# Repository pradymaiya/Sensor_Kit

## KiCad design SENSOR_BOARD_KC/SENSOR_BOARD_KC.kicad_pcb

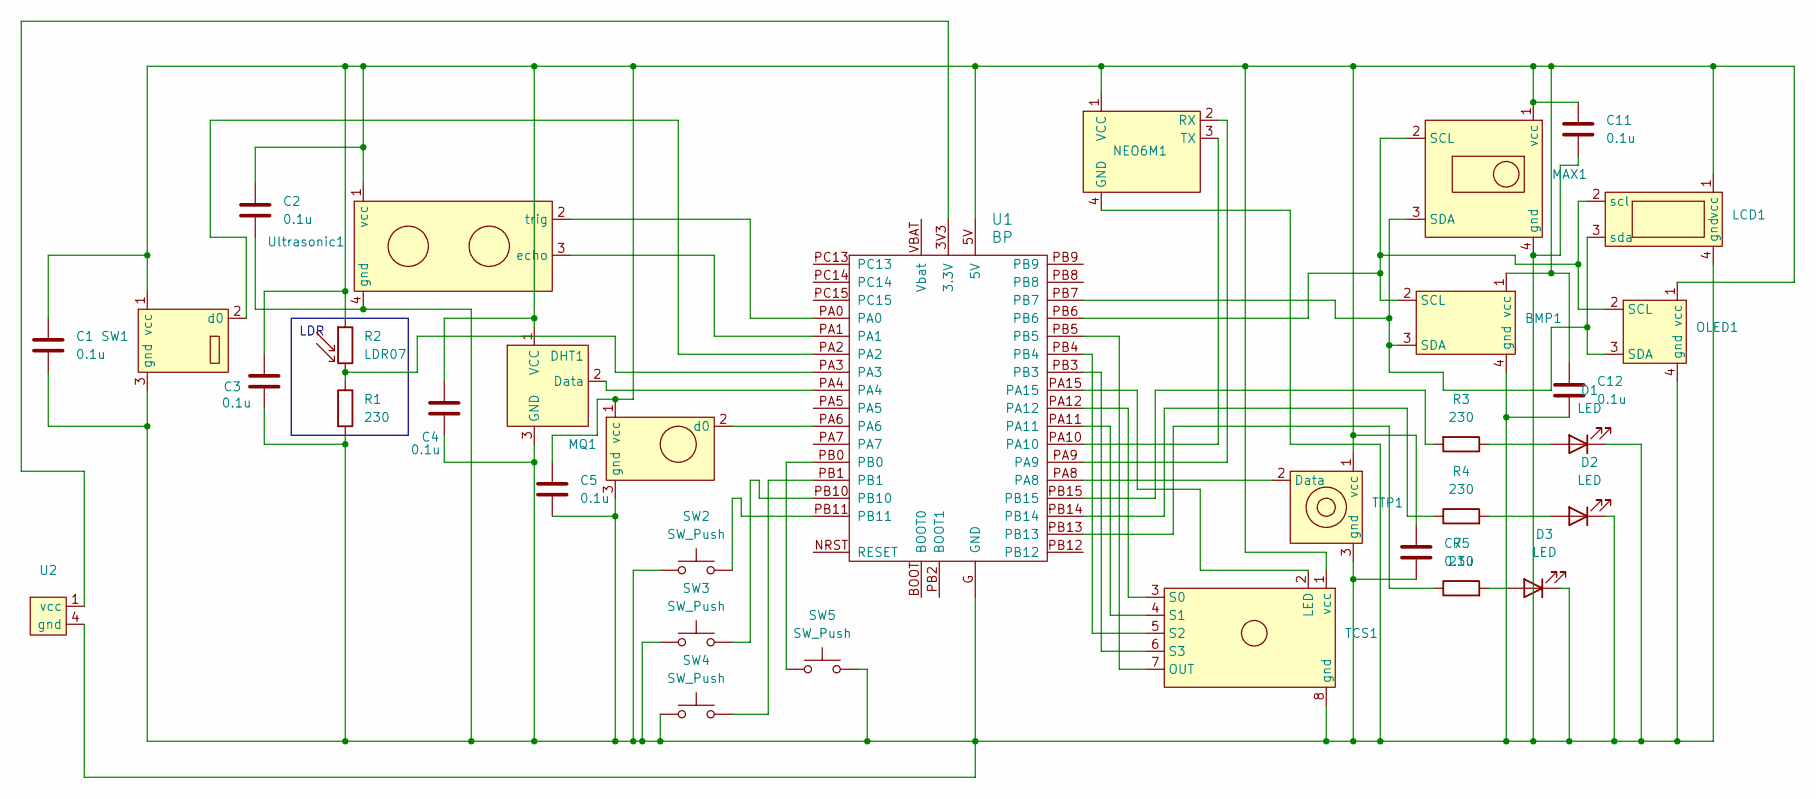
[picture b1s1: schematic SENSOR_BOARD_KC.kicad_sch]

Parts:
BMP1: BMP180
C1, C2, C3, C4, C5, C7, C11, C12: 0.1u; C_Disc_D5.0mm_W2.5mm_P2.50mm
D1, D2, D3: LED; LED_D3.0mm
DHT1: DHT11
LCD1: LCD_I2C
MAX1: MAX30100
MQ1: MQ2
NEO6M1: Neo-6M
OLED1: 128x64OLED
R1, R3, R4, R5: 230; R_Axial_DIN0207_L6.3mm_D2.5mm_P10.16mm_Horizontal
R2: LDR07; R_LDR_5.1x4.3mm_P3.4mm_Vertical
SW1: SW420
SW2, SW3, SW4, SW5: SW_Push; Switch
TCS1: TCS3200
TTP1: TTP223
U1: BP; blue_pill
U2: STLINK_Connect
Ultrasonic1: HC-SR04

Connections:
unnamed: BMP1.2 (SCL), LCD1.2 (scl), MAX1.2 (SCL), OLED1.2 (SCL), U1.PB6
unnamed: BMP1.3 (SDA), LCD1.3 (sda), MAX1.3 (SDA), OLED1.3 (SDA), U1.PB7
unnamed: BMP1.4 (gnd), C1.2, C2.2, C3.2, C4.2, C5.2, C7.2, C11.2, C12.2, D1.1 (K), D2.1 (K), D3.1 (K), DHT1.3 (GND), LCD1.4 (gnd), MAX1.4 (gnd), MQ1.3 (gnd), NEO6M1.4 (GND), OLED1.4 (gnd), R1.2, SW1.3 (gnd), SW2.1, SW3.1, SW4.1, SW5.2, TCS1.8 (gnd), TTP1.3 (gnd), U1.G (GND), U2.4 (gnd), Ultrasonic1.4 (gnd)
unnamed: BMP1.1 (vcc), C1.1, C2.1, C3.1, C4.1, C5.1, C7.1, C11.1, C12.1, DHT1.1 (VCC), LCD1.1 (vcc), MAX1.1 (vcc), MQ1.1 (vcc), NEO6M1.1 (VCC), OLED1.1 (vcc), R2.1, SW1.1 (vcc), TCS1.1 (vcc), TTP1.1 (vcc), U1.5V, Ultrasonic1.1 (vcc)
unnamed: D1.2 (A), R3.1
unnamed: D2.2 (A), R4.2
unnamed: D3.2 (A), R5.2
unnamed: DHT1.2 (Data), U1.PA4
unnamed: MQ1.2 (d0), U1.PA6
unnamed: NEO6M1.2 (RX), U1.PA9
unnamed: NEO6M1.3 (TX), U1.PA10
unnamed: R1.1, R2.2, U1.PA3
unnamed: R3.2, U1.PB15
unnamed: R4.1, U1.PB14
unnamed: R5.1, U1.PB13
unnamed: SW1.2 (d0), U1.PA2
unnamed: SW2.2, U1.PB11
unnamed: SW3.2, U1.PB10
unnamed: SW4.2, U1.PB1
unnamed: SW5.1, U1.PB0
unnamed: TCS1.2 (LED), U1.PA15
unnamed: TCS1.7 (OUT), U1.PB5
unnamed: TCS1.3 (S0), U1.PA12
unnamed: TCS1.4 (S1), U1.PA11
unnamed: TCS1.5 (S2), U1.PB4
unnamed: TCS1.6 (S3), U1.PB3
unnamed: TTP1.2 (Data), U1.PA8
unnamed: U1.3V3 (3.3V), U2.1 (vcc)
unnamed: U1.PA1, Ultrasonic1.3 (echo)
unnamed: U1.PA0, Ultrasonic1.2 (trig)

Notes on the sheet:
LDR

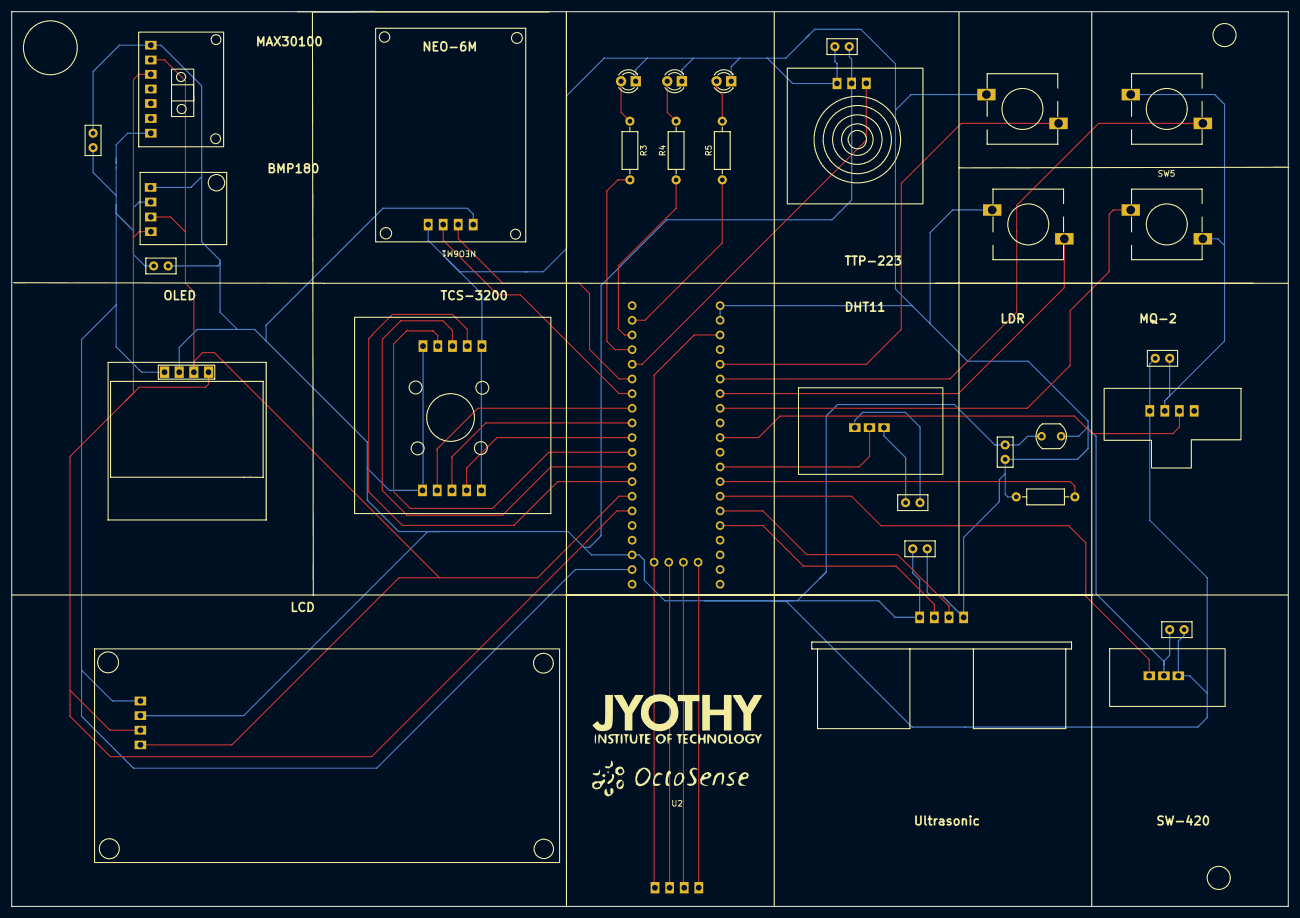
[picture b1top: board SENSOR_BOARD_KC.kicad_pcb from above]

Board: 2 copper layers, 221.2 x 155.0 mm, 33 parts (0 on the bottom side), 30 nets.

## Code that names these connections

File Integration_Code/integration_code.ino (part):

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Adafruit_SSD1306 display(SCREEN_WIDTH, SCREEN_HEIGHT, &Wire, OLED_RESET);

// Sensor Definitions
#define MQ2_ANALOG_PIN PA6
#define TOUCH_PIN PA8       // Touch sensor
#define BUTTON_INC PB10     // Increment button
#define BUTTON_DEC PB1      // Decrement button
#define BUTTON_ENTER PB0    // Enter button
#define TRIG_PIN PA0        // Ultrasonic sensor trig pin
#define ECHO_PIN PA1        // Ultrasonic sensor echo pin
#define LDR_PIN PA3         // LDR sensor pin
#define VIBRATION_PIN PA2   // Vibration sensor pin
#define DHT_PIN PA4         // DHT sensor pin
#define DHT_TYPE DHT11
DHT dht(DHT_PIN, DHT_TYPE);
#define S0 PB13
#define S1 PB14
#define S2 PB4
#define S3 PB3
#define sensorOut PB5


// BMP180 Sensor
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
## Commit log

2024-12-27 PCB design file uploaded with code
2024-12-27 Documents added
2024-12-28 Some changes in pcb
2024-12-30 workings of 6 sensors
2024-12-31 some changes
